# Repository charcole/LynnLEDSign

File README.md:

# Lynn Sign

Just a little gift I made for someone (who you might guess is called Lynn).

45 LEDs with a range of transition effects.

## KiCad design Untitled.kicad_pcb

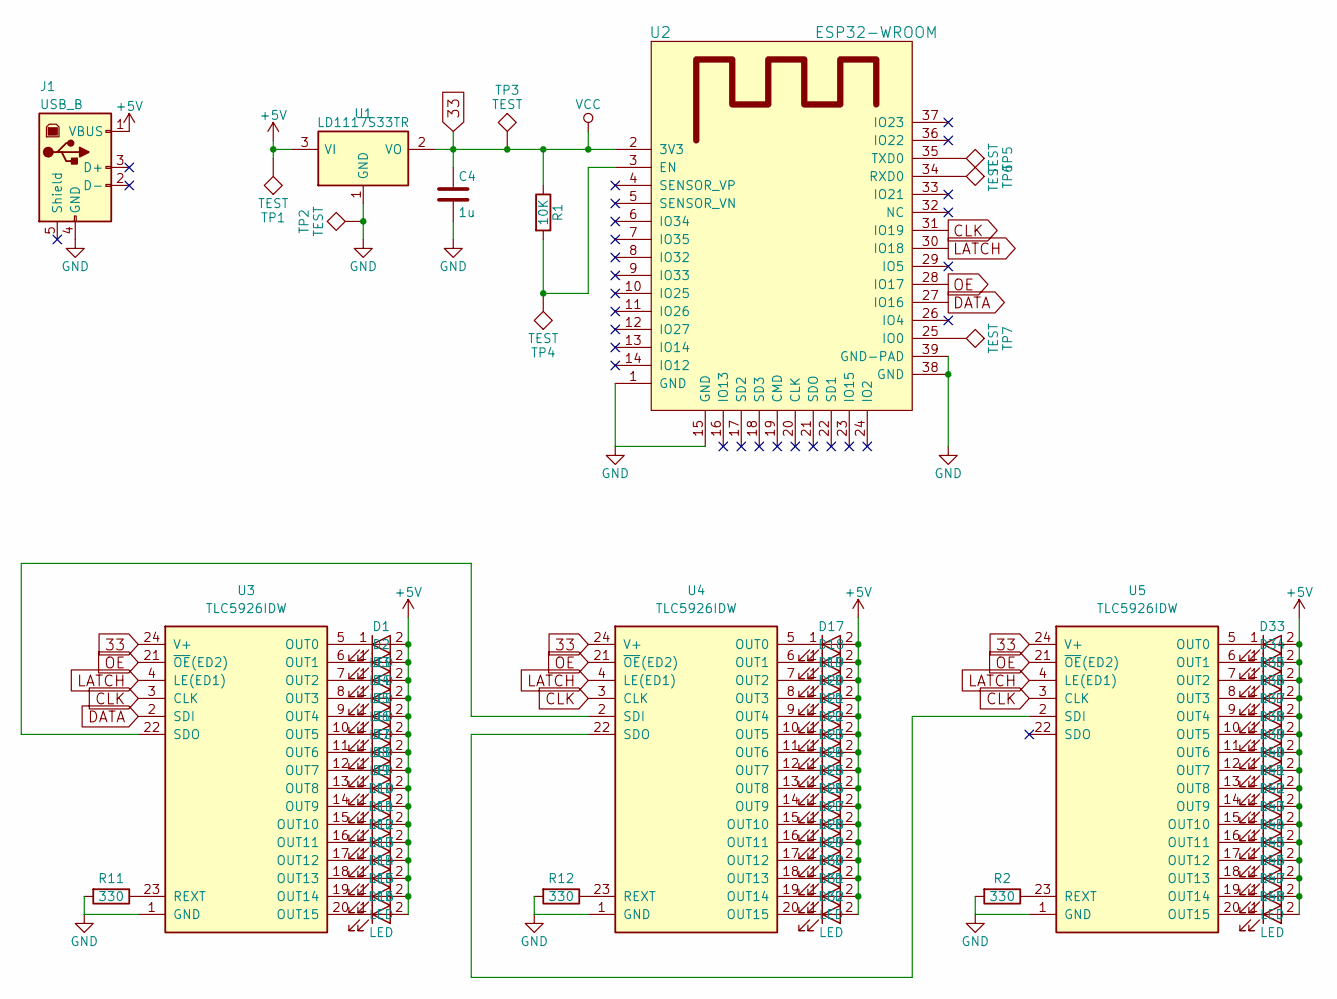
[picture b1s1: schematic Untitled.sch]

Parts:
C4: 1u; C_1206_HandSoldering
D1, D2, D3, D4, D5, D6, D7, D8, D9, D10, D11, D12, D13, D14, D15, D16, D17, D18, D19, D20, D21, D22, D23, D24, D25, D26, D27, D28, D29, D30, D31, D32, D33, D34, D35, D36, D37, D38, D39, D40, D41, D42, D43, D44, D45, D46, D47, D48: LED; LED_1206_HandSoldering
J1: USB_B; USB_Mini-B
R1: 10K; R_1206_HandSoldering
R2, R11, R12: 330; R_1206_HandSoldering
TP1, TP3, TP4, TP5, TP6, TP7: TEST; Measurement_Point_Round-SMD-Pad_Small
TP2: TEST; Measurement_Point_Square-SMD-Pad_Small
U1: LD1117S33TR; SOT-223
U2: ESP32-WROOM
U3, U4, U5: TLC5926IDW; SOIC-24W_7.5x15.4mm_Pitch1.27mm; MPN TLC5926IDW

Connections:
33: C4.1, R1.1, TP3.1, U1.2 (VO), U2.2 (3V3), U3.24 (V+), U4.24 (V+), U5.24 (V+)
+5V: D1.2 (A), D2.2 (A), D3.2 (A), D4.2 (A), D5.2 (A), D6.2 (A), D7.2 (A), D8.2 (A), D9.2 (A), D10.2 (A), D11.2 (A), D12.2 (A), D13.2 (A), D14.2 (A), D15.2 (A), D16.2 (A), D17.2 (A), D18.2 (A), D19.2 (A), D20.2 (A), D21.2 (A), D22.2 (A), D23.2 (A), D24.2 (A), D25.2 (A), D26.2 (A), D27.2 (A), D28.2 (A), D29.2 (A), D30.2 (A), D31.2 (A), D32.2 (A), D33.2 (A), D34.2 (A), D35.2 (A), D36.2 (A), D37.2 (A), D38.2 (A), D39.2 (A), D40.2 (A), D41.2 (A), D42.2 (A), D43.2 (A), D44.2 (A), D45.2 (A), D46.2 (A), D47.2 (A), D48.2 (A), J1.1 (VBUS), TP1.1, U1.3 (VI)
CLK: U2.31 (IO19), U3.3 (CLK), U4.3 (CLK), U5.3 (CLK)
DATA: U2.27 (IO16), U3.2 (SDI)
GND: C4.2, J1.4 (GND), R2.2, R11.2, R12.2, TP2.1, U1.1 (GND), U2.1 (GND), U2.15 (GND), U2.38 (GND), U2.39 (GND-PAD), U3.1 (GND), U4.1 (GND), U5.1 (GND)
LATCH: U2.30 (IO18), U3.4 (LE(ED1)), U4.4 (LE(ED1)), U5.4 (LE(ED1))
unnamed: D1.1 (K), U3.5 (OUT0)
unnamed: D2.1 (K), U3.6 (OUT1)
unnamed: D3.1 (K), U3.7 (OUT2)
unnamed: D4.1 (K), U3.8 (OUT3)
unnamed: D5.1 (K), U3.9 (OUT4)
unnamed: D6.1 (K), U3.10 (OUT5)
unnamed: D7.1 (K), U3.11 (OUT6)
unnamed: D8.1 (K), U3.12 (OUT7)
unnamed: D9.1 (K), U3.13 (OUT8)
unnamed: D10.1 (K), U3.14 (OUT9)
unnamed: D11.1 (K), U3.15 (OUT10)
unnamed: D12.1 (K), U3.16 (OUT11)
unnamed: D13.1 (K), U3.17 (OUT12)
unnamed: D14.1 (K), U3.18 (OUT13)
unnamed: D15.1 (K), U3.19 (OUT14)
unnamed: D16.1 (K), U3.20 (OUT15)
unnamed: D17.1 (K), U4.5 (OUT0)
unnamed: D18.1 (K), U4.6 (OUT1)
unnamed: D19.1 (K), U4.7 (OUT2)
unnamed: D20.1 (K), U4.8 (OUT3)
unnamed: D21.1 (K), U4.9 (OUT4)
unnamed: D22.1 (K), U4.10 (OUT5)
unnamed: D23.1 (K), U4.11 (OUT6)
unnamed: D24.1 (K), U4.12 (OUT7)
unnamed: D25.1 (K), U4.13 (OUT8)
unnamed: D26.1 (K), U4.14 (OUT9)
unnamed: D27.1 (K), U4.15 (OUT10)
unnamed: D28.1 (K), U4.16 (OUT11)
unnamed: D29.1 (K), U4.17 (OUT12)
unnamed: D30.1 (K), U4.18 (OUT13)
unnamed: D31.1 (K), U4.19 (OUT14)
unnamed: D32.1 (K), U4.20 (OUT15)
unnamed: D33.1 (K), U5.5 (OUT0)
unnamed: D34.1 (K), U5.6 (OUT1)
unnamed: D35.1 (K), U5.7 (OUT2)
unnamed: D36.1 (K), U5.8 (OUT3)
unnamed: D37.1 (K), U5.9 (OUT4)
unnamed: D38.1 (K), U5.10 (OUT5)
unnamed: D39.1 (K), U5.11 (OUT6)
unnamed: D40.1 (K), U5.12 (OUT7)
unnamed: D41.1 (K), U5.13 (OUT8)
unnamed: D42.1 (K), U5.14 (OUT9)
unnamed: D43.1 (K), U5.15 (OUT10)
unnamed: D44.1 (K), U5.16 (OUT11)
unnamed: D45.1 (K), U5.17 (OUT12)
unnamed: D46.1 (K), U5.18 (OUT13)
unnamed: D47.1 (K), U5.19 (OUT14)
unnamed: D48.1 (K), U5.20 (OUT15)
unnamed: R1.2, TP4.1, U2.3 (EN)
unnamed: R2.1, U5.23 (REXT)
unnamed: R11.1, U3.23 (REXT)
unnamed: R12.1, U4.23 (REXT)
unnamed: TP5.1, U2.35 (TXD0)
unnamed: TP6.1, U2.34 (RXD0)
unnamed: TP7.1, U2.25 (IO0)
unnamed: U3.22 (SDO), U4.2 (SDI)
unnamed: U4.22 (SDO), U5.2 (SDI)
OE: U2.28 (IO17), U3.21 (~OE~(ED2)), U4.21 (~OE~(ED2)), U5.21 (~OE~(ED2))

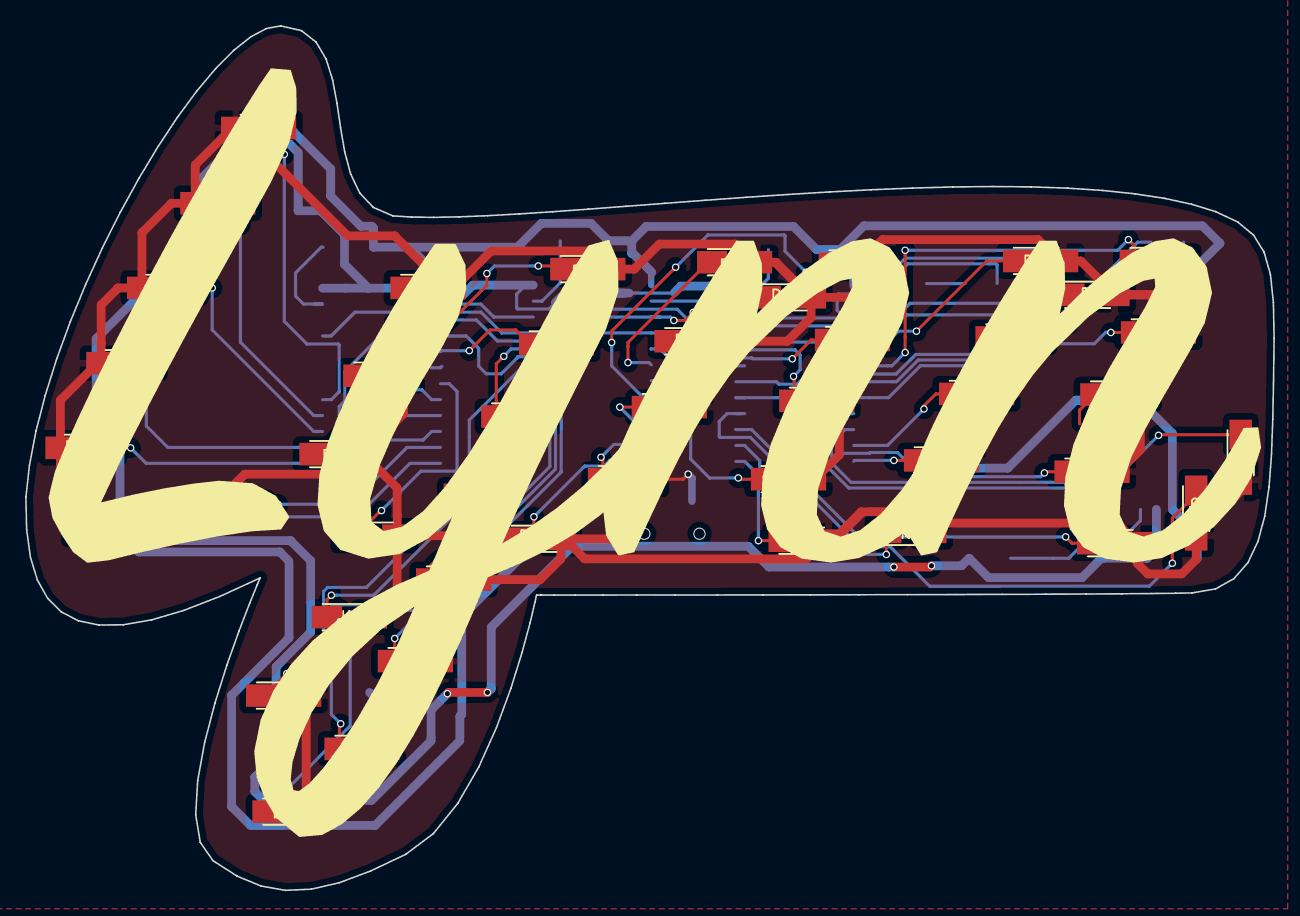
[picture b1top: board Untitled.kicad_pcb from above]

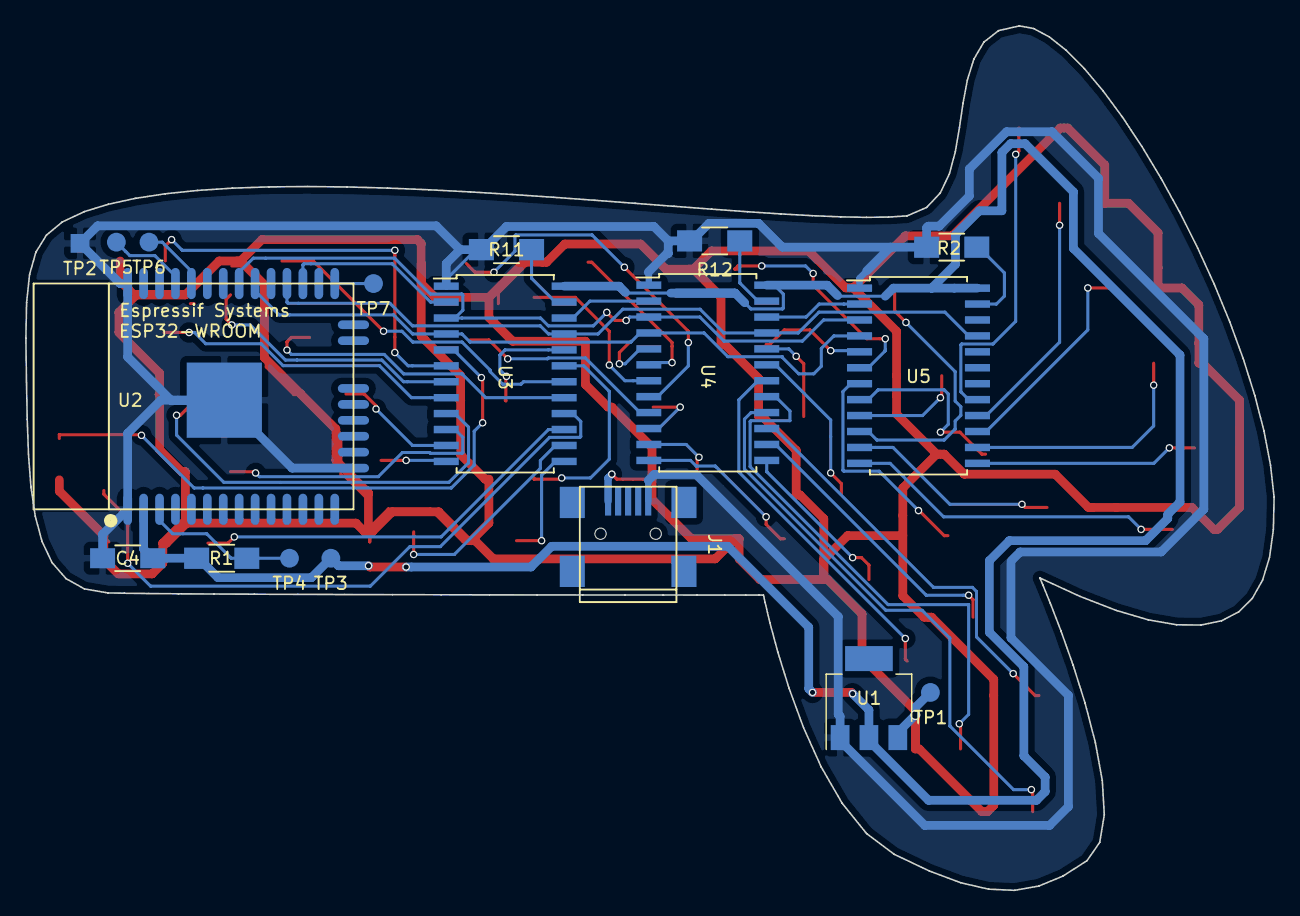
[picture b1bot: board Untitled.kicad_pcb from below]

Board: 2 copper layers, 99.5 x 68.9 mm, 64 parts (18 on the bottom side), 61 nets.

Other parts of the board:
lynn_outline: G***; lynn_outline

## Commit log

2018-01-30 Lynn almost done
2018-01-30 Lynn V1
2018-01-31 Finished board?
2018-01-31 Increased power line thickness
2018-01-31 Made shorter to fit within limits
2018-02-10 First working firmware
2018-02-10 Fix for incorrect GND pad on mini usb connector
2018-02-13 Final tweaks
2018-02-15 Renamed Untitled to Lynn
2018-02-15 Renamed and removed unneeded files
2018-02-15 3D model of the board
2018-02-15 Source SVG for silkscreen and board cut
2018-02-15 Added README
2018-02-15 Added build directory to gitignore
2018-02-15 Added LICENSE
